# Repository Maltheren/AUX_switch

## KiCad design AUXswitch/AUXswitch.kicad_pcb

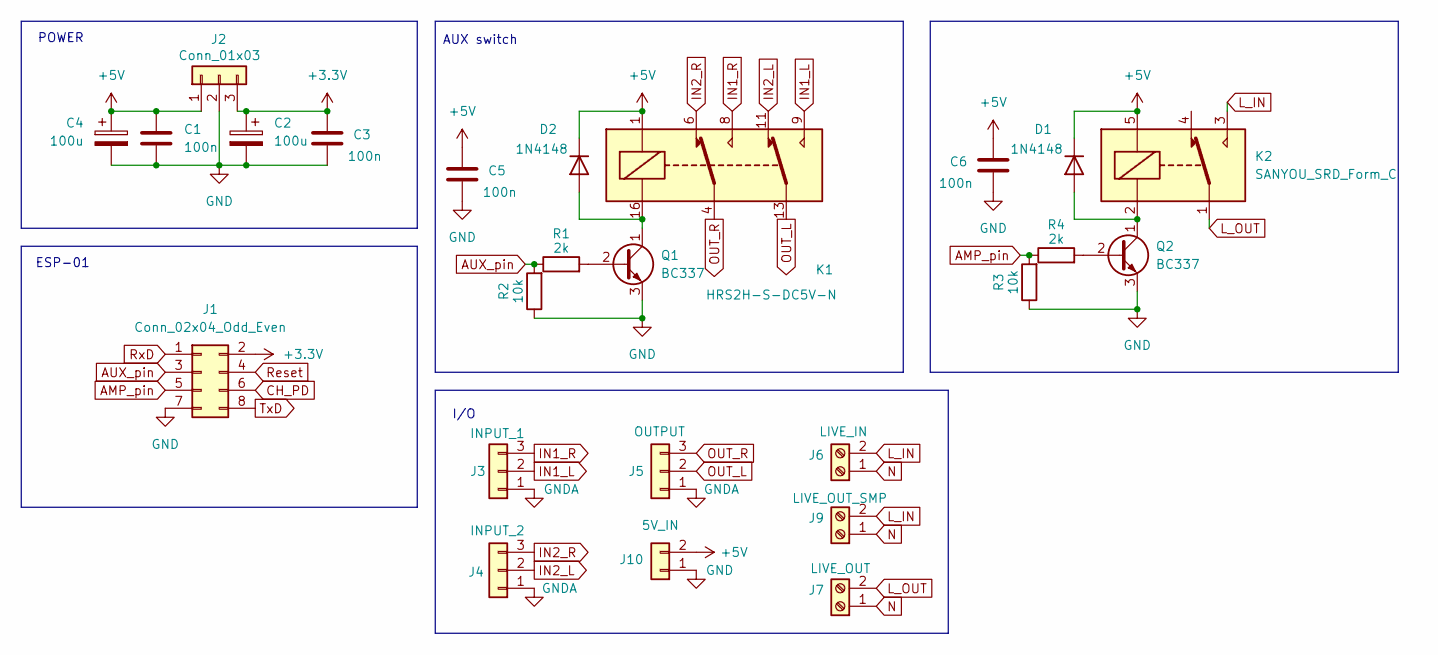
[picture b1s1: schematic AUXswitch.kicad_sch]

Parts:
C1, C3, C5, C6: 100n; C_Disc_D4.3mm_W1.9mm_P5.00mm
C2, C4: 100u; CP_Radial_Tantal_D4.5mm_P2.50mm
D1, D2: 1N4148; D_DO-35_SOD27_P7.62mm_Horizontal
J1: Conn_02x04_Odd_Even; PinHeader_2x04_P2.54mm_Vertical
J2: Conn_01x03; PinSocket_1x03_P1.27mm_Vertical
J3: INPUT_1; FanPinHeader_1x03_P2.54mm_Vertical
J4: INPUT_2; FanPinHeader_1x03_P2.54mm_Vertical
J5: OUTPUT; FanPinHeader_1x03_P2.54mm_Vertical
J6: LIVE_IN; Altech_AK100_1x02_P5.00mm
J7: LIVE_OUT; Altech_AK100_1x02_P5.00mm
J9: LIVE_OUT_SMP; Altech_AK100_1x02_P5.00mm
J10: 5V_IN; JST_EH_B2B-EH-A_1x02_P2.50mm_Vertical
K1: HRS2H-S-DC5V-N; Relay_DPDT_Omron_G5V-2
K2: SANYOU_SRD_Form_C; Relay_SPDT_SANYOU_SRD_Series_Form_C
Q1, Q2: BC337; TO-92_Inline
R1, R4: 2k; R_Axial_DIN0204_L3.6mm_D1.6mm_P5.08mm_Horizontal
R2, R3: 10k; R_Axial_DIN0204_L3.6mm_D1.6mm_P5.08mm_Horizontal

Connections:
+3.3V: C2.1, C3.1, J1.2, J2.3
+5V: C1.1, C4.1, C5.1, C6.1, D1.1 (K), D2.1 (K), J2.1, J10.2, K1.1, K2.5
AMP_pin: J1.5, R3.2, R4.1
AUX_pin: J1.3, R1.1, R2.2
CH_PD: J1.6
GND: C1.2, C2.2, C3.2, C4.2, C5.2, C6.2, J1.7, J2.2, J10.1, Q1.3 (E), Q2.3 (E), R2.1, R3.1
GNDA: J3.1, J4.1, J5.1
IN1_L: J3.2, K1.9
IN1_R: J3.3, K1.8
IN2_L: J4.2, K1.11
IN2_R: J4.3, K1.6
L_IN: J6.2, J9.2, K2.3
L_OUT: J7.2, K2.1
N: J6.1, J7.1, J9.1
unnamed: D1.2 (A), K2.2, Q2.1 (C)
unnamed: D2.2 (A), K1.16, Q1.1 (C)
unnamed: Q1.2 (B), R1.2
unnamed: Q2.2 (B), R4.2
OUT_L: J5.2, K1.13
OUT_R: J5.3, K1.4
Reset: J1.4
RxD: J1.1
TxD: J1.8

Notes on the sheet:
AUX switch
POWER
I/O
ESP-01

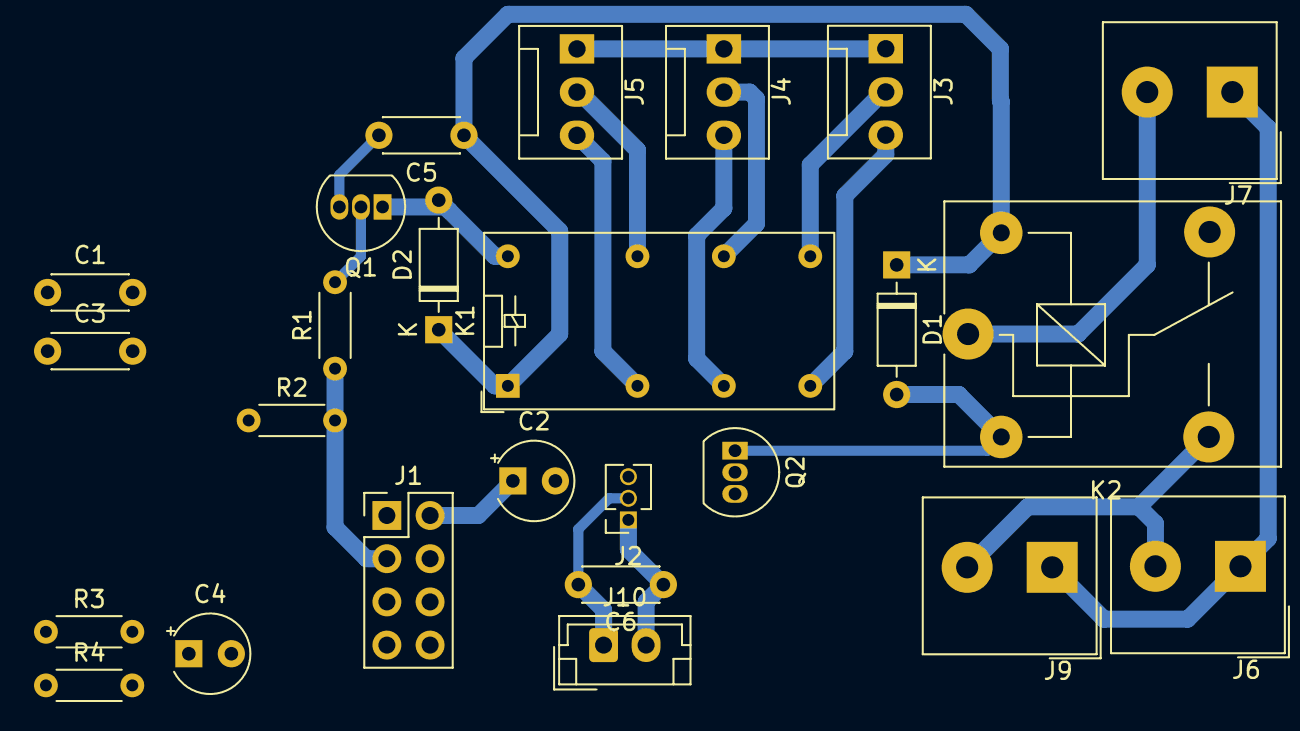
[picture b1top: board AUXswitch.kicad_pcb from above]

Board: 2 copper layers, 25 parts (0 on the bottom side), 19 nets.

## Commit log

2024-08-26 første push
2024-08-26 fixede pinouts
